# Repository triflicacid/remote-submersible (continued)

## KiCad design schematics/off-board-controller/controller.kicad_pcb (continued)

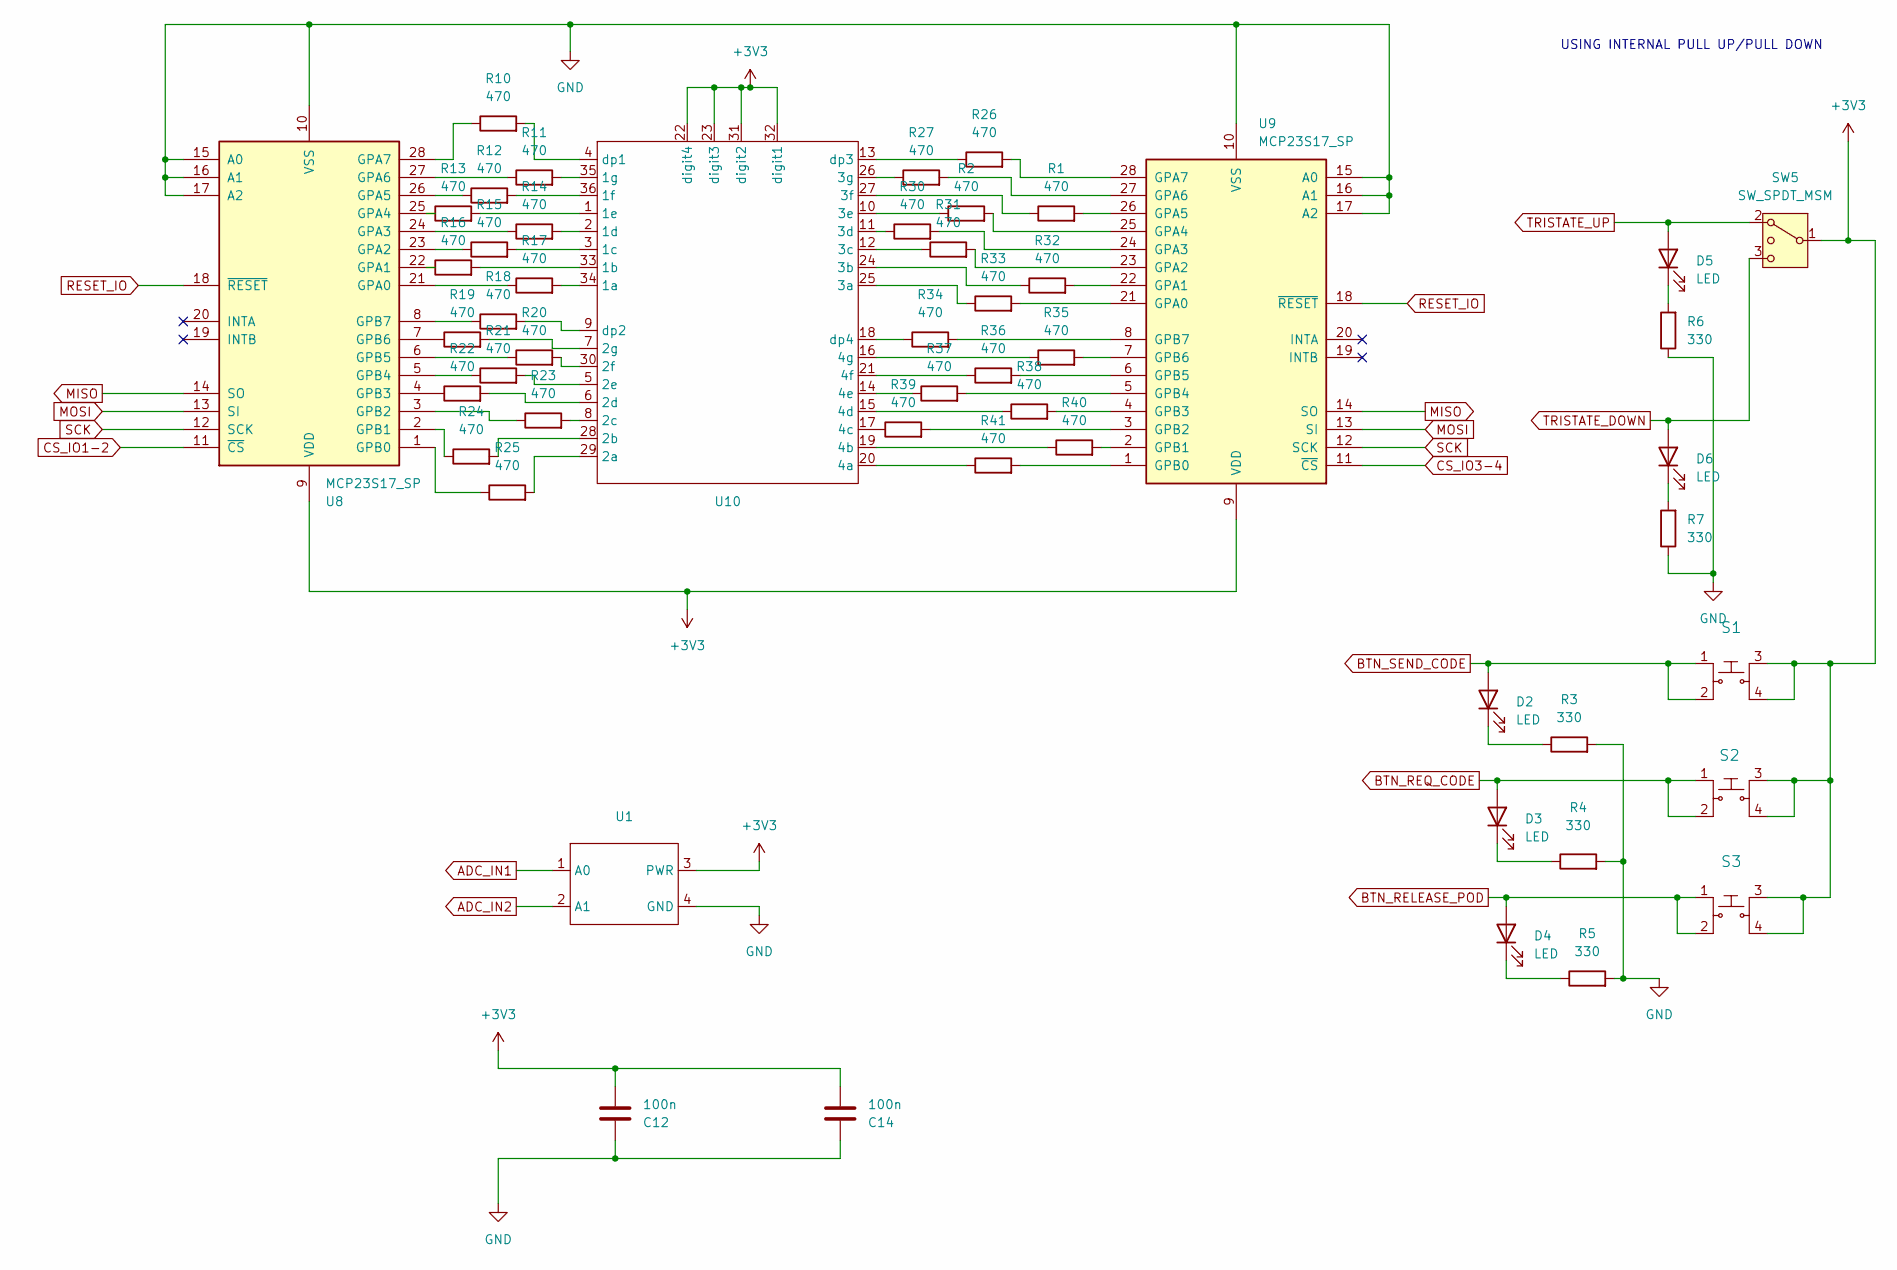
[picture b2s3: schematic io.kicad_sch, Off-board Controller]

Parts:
C12, C14: 100n; C_0805_2012Metric_Pad1.18x1.45mm_HandSolder
D2, D3, D4, D5, D6: LED; LED_0805_2012Metric_Pad1.15x1.40mm_HandSolder
R1, R2, R10, R11, R12, R13, R14, R15, R16, R17, R18, R19, R20, R21, R22, R23, R24, R25, R26, R27, R30, R31, R32, R33, R34, R35, R36, R37, R38, R39, R40, R41: 470; R_0805_2012Metric_Pad1.20x1.40mm_HandSolder
R3, R4, R5, R6, R7: 330; R_0805_2012Metric_Pad1.20x1.40mm_HandSolder
S1, S2, S3: button; MPN 1825910-6; Digi-Key_PN 450-1650-ND
SW5: SW_SPDT_MSM; spdt
U1: NS-Tech_Grove_1x04_P2mm_Vertical
U8, U9: MCP23S17_SP; DIP-28_W7.62mm
U10: seven_segment

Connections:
+3V3: C12.2, C14.2, S1.3, S1.4, S2.3, S2.4, S3.3, S3.4, SW5.1 (3), U1.3 (PWR), U8.9 (VDD), U9.9 (VDD), U10.22 (digit4), U10.23 (digit3), U10.31 (digit2), U10.32 (digit1); also elsewhere on the board
ADC_IN1: U1.1 (A0); also elsewhere on the board
ADC_IN2: U1.2 (A1); also elsewhere on the board
BTN_RELEASE_POD: D4.2 (A), S3.1, S3.2; also elsewhere on the board
BTN_REQ_CODE: D3.2 (A), S2.1, S2.2; also elsewhere on the board
BTN_SEND_CODE: D2.2 (A), S1.1, S1.2; also elsewhere on the board
CS_IO1-2: U8.11 (~CS); also elsewhere on the board
CS_IO3-4: U9.11 (~CS); also elsewhere on the board
GND: C12.1, C14.1, R3.2, R4.2, R5.2, R6.1, R7.1, U1.4 (GND), U8.10 (VSS), U8.15 (A0), U8.16 (A1), U8.17 (A2), U9.10 (VSS), U9.15 (A0), U9.16 (A1), U9.17 (A2); also elsewhere on the board
MISO: U8.14 (SO), U9.14 (SO); also elsewhere on the board
MOSI: U8.13 (SI), U9.13 (SI); also elsewhere on the board
unnamed: D2.1 (K), R3.1
unnamed: D3.1 (K), R4.1
unnamed: D4.1 (K), R5.1
unnamed: D5.1 (K), R6.2
unnamed: D6.1 (K), R7.2
unnamed: R17.1, U8.21 (GPA0)
unnamed: R16.1, U8.22 (GPA1)
unnamed: R15.1, U8.23 (GPA2)
unnamed: R14.1, U8.24 (GPA3)
unnamed: R13.1, U8.25 (GPA4)
unnamed: R12.1, U8.26 (GPA5)
unnamed: R11.1, U8.27 (GPA6)
unnamed: R10.1, U8.28 (GPA7)
unnamed: R25.1, U8.1 (GPB0)
unnamed: R24.1, U8.2 (GPB1)
unnamed: R23.1, U8.3 (GPB2)
unnamed: R22.1, U8.4 (GPB3)
unnamed: R21.1, U8.5 (GPB4)
unnamed: R20.1, U8.6 (GPB5)
unnamed: R19.1, U8.7 (GPB6)
unnamed: R18.1, U8.8 (GPB7)
unnamed: R33.2, U9.21 (GPA0)
unnamed: R32.2, U9.22 (GPA1)
unnamed: R31.2, U9.23 (GPA2)
unnamed: R30.2, U9.24 (GPA3)
unnamed: R2.2, U9.25 (GPA4)
unnamed: R1.2, U9.26 (GPA5)
unnamed: R27.2, U9.27 (GPA6)
unnamed: R26.2, U9.28 (GPA7)
unnamed: R41.2, U9.1 (GPB0)
unnamed: R40.2, U9.2 (GPB1)
unnamed: R39.2, U9.3 (GPB2)
unnamed: R38.2, U9.4 (GPB3)
unnamed: R37.2, U9.5 (GPB4)
unnamed: R36.2, U9.6 (GPB5)
unnamed: R35.2, U9.7 (GPB6)
unnamed: R34.2, U9.8 (GPB7)
unnamed: R17.2, U10.34 (1a)
unnamed: R16.2, U10.33 (1b)
unnamed: R15.2, U10.3 (1c)
unnamed: R14.2, U10.2 (1d)
unnamed: R13.2, U10.1 (1e)
unnamed: R12.2, U10.36 (1f)
unnamed: R11.2, U10.35 (1g)
unnamed: R25.2, U10.29 (2a)
unnamed: R24.2, U10.28 (2b)
unnamed: R23.2, U10.8 (2c)
unnamed: R22.2, U10.6 (2d)
unnamed: R21.2, U10.5 (2e)
unnamed: R20.2, U10.30 (2f)
unnamed: R19.2, U10.7 (2g)
unnamed: R33.1, U10.25 (3a)
unnamed: R32.1, U10.24 (3b)
unnamed: R31.1, U10.12 (3c)
unnamed: R30.1, U10.11 (3d)
unnamed: R2.1, U10.10 (3e)
unnamed: R1.1, U10.27 (3f)
unnamed: R27.1, U10.26 (3g)
unnamed: R41.1, U10.20 (4a)
unnamed: R40.1, U10.19 (4b)
unnamed: R39.1, U10.17 (4c)
unnamed: R38.1, U10.15 (4d)
unnamed: R37.1, U10.14 (4e)
unnamed: R36.1, U10.21 (4f)
unnamed: R35.1, U10.16 (4g)
unnamed: R10.2, U10.4 (dp1)
unnamed: R18.2, U10.9 (dp2)
unnamed: R26.1, U10.13 (dp3)
unnamed: R34.1, U10.18 (dp4)
RESET_IO: U8.18 (~RESET), U9.18 (~RESET); also elsewhere on the board
SCK: U8.12 (SCK), U9.12 (SCK); also elsewhere on the board
TRISTATE_DOWN: D6.2 (A), SW5.3 (4); also elsewhere on the board
TRISTATE_UP: D5.2 (A), SW5.2 (1); also elsewhere on the board

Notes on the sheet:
USING INTERNAL PULL UP/PULL DOWN

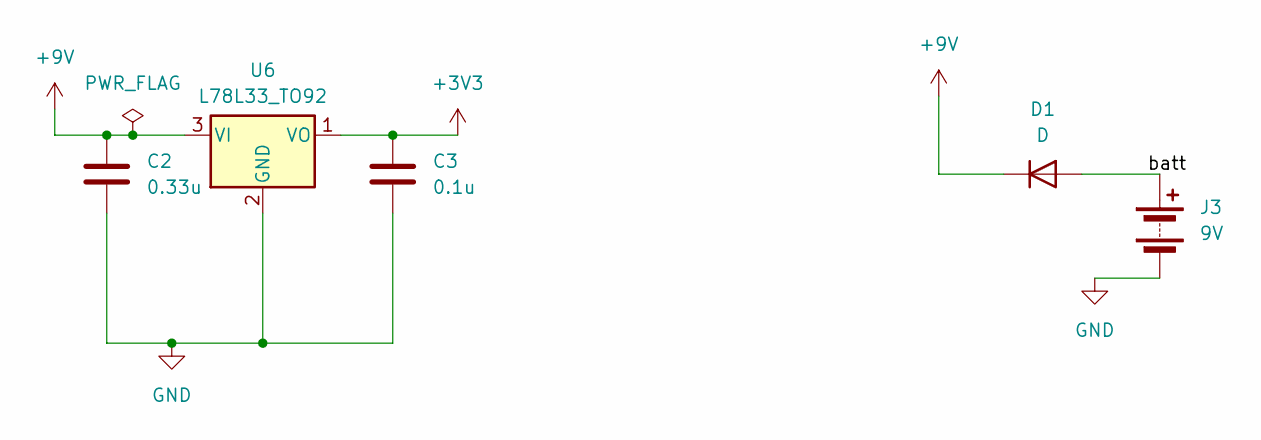
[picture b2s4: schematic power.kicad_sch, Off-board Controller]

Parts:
C2: 0.33u; C_0805_2012Metric_Pad1.18x1.45mm_HandSolder
C3: 0.1u; C_0805_2012Metric_Pad1.18x1.45mm_HandSolder
D1: D; D_A-405_P7.62mm_Horizontal
J3: 9V; PinSocket_1x02_P2.54mm_Vertical
U6: L78L33_TO92; TO-92_Inline

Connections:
+3V3: C3.1, U6.1 (VO); also elsewhere on the board
+9V: C2.1, D1.1 (K), U6.3 (VI)
/power/batt: D1.2 (A), J3.1 (+)
GND: C2.2, C3.2, J3.2 (-), U6.2 (GND); also elsewhere on the board

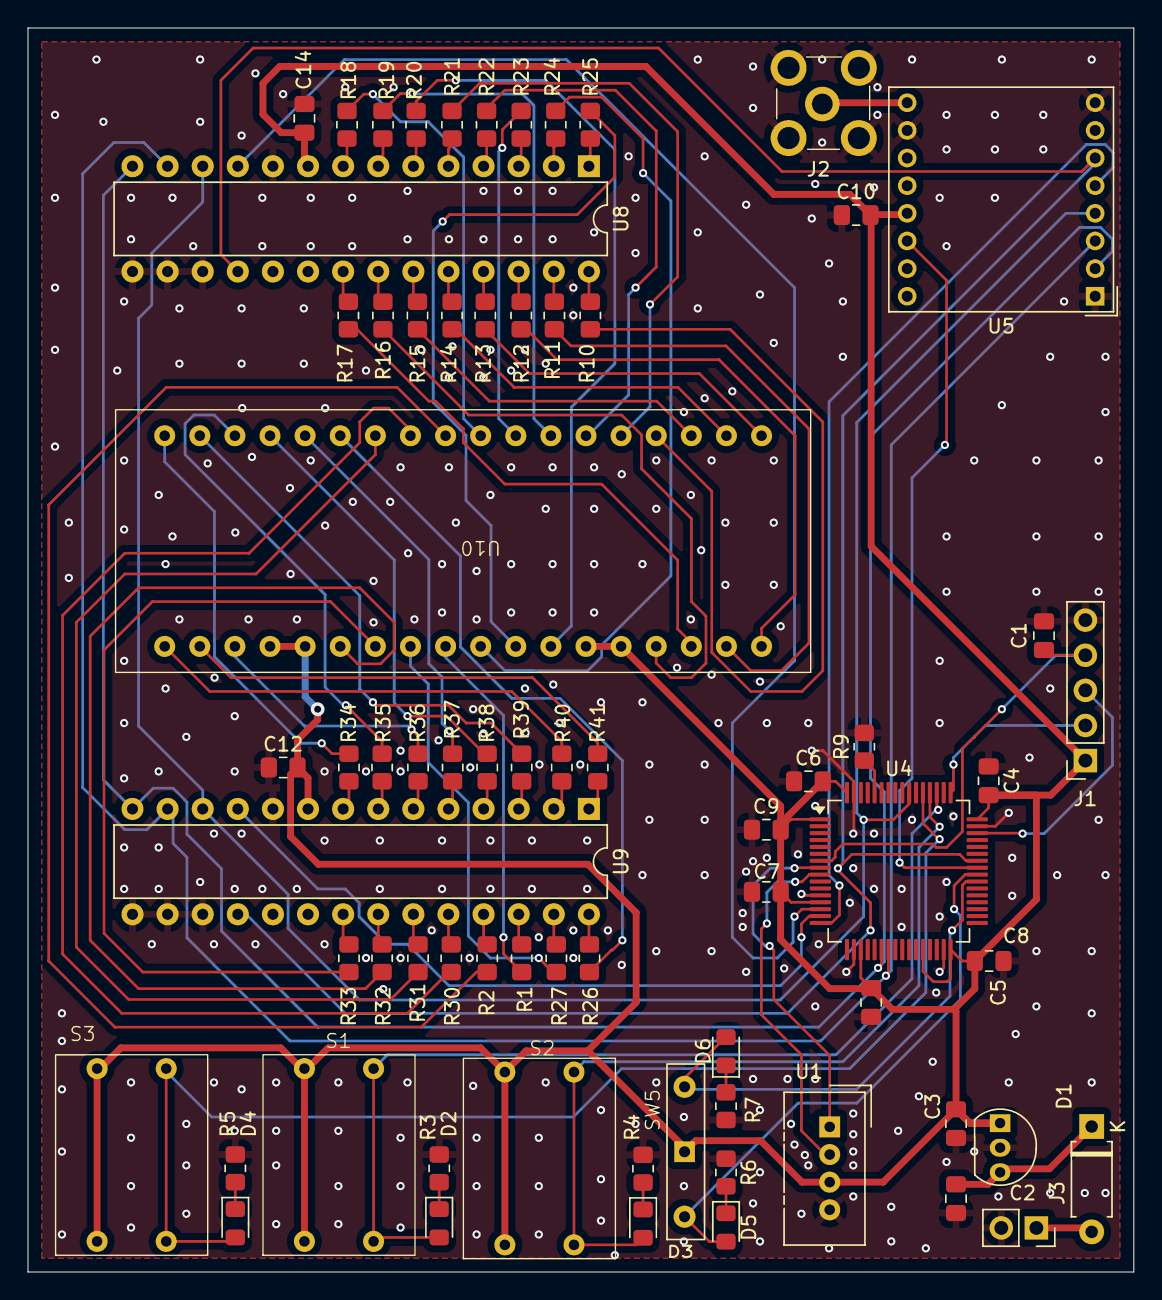
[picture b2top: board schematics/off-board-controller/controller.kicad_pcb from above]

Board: 2 copper layers, 80.0 x 90.0 mm, 70 parts (0 on the bottom side), 93 nets.

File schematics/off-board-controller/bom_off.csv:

Reference,Value,Datasheet,Footprint,Qty,DNP
"C1,C4,C5,C6,C7,C8,C9,C10,C12,C14",100n,~,Capacitor_SMD:C_0805_2012Metric_Pad1.18x1.45mm_HandSolder,10,
C2,0.33u,~,Capacitor_SMD:C_0805_2012Metric_Pad1.18x1.45mm_HandSolder,1,
C3,0.1u,~,Capacitor_SMD:C_0805_2012Metric_Pad1.18x1.45mm_HandSolder,1,
D1,D,~,Diode_THT:D_A-405_P7.62mm_Horizontal,1,
"D2,D3,D4,D5,D6",LED,~,LED_SMD:LED_0805_2012Metric_Pad1.15x1.40mm_HandSolder,5,
J1,programmer,~,Connector_PinSocket_2.54mm:PinSocket_1x05_P2.54mm_Vertical,1,
J2,5-1814832-1,https://www.te.com/commerce/DocumentDelivery/DDEController?A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,digikey-footprints:RF_SMA_Vertical_5-1814832-1,1,
J3,9V,~,Connector_PinSocket_2.54mm:PinSocket_1x02_P2.54mm_Vertical,1,
"R1,R2,R10,R11,R12,R13,R14,R15,R16,R17,R18,R19,R20,R21,R22,R23,R24,R25,R26,R27,R30,R31,R32,R33,R34,R35,R36,R37,R38,R39,R40,R41",470,~,Resistor_SMD:R_0805_2012Metric_Pad1.20x1.40mm_HandSolder,32,
"R3,R4,R5,R6,R7",330,~,Resistor_SMD:R_0805_2012Metric_Pad1.20x1.40mm_HandSolder,5,
R9,10k,~,Resistor_SMD:R_0805_2012Metric_Pad1.20x1.40mm_HandSolder,1,
"S1,S2,S3,U1,U10",~,,-- mixed values --,5,
SW5,SW_SPDT_MSM,~,sub:spdt,1,
U4,STM32L476RGTx,https://www.st.com/resource/en/datasheet/stm32l476rg.pdf,Package_QFP:LQFP-64_10x10mm_P0.5mm,1,
U5,RFM98W-433S2,https://www.hoperf.com/data/upload/portal/20181127/5bfcdb5e1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,RF_Module:HOPERF_RFM9XW_THT,1,
U6,L78L33_TO92,http://www.st.com/content/ccc/resource/technical/document/da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,Package_TO_SOT_THT:TO-92_Inline,1,
"U8,U9",MCP23S17_SP,http://ww1.microchip.com/downloads/en/DeviceDoc/20001952C.pdf,Package_DIP:DIP-28_W7.62mm,2,

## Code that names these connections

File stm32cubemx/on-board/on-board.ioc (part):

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Mcu.Name=STM32L476R(C-E-G)Tx
Mcu.Package=LQFP64
Mcu.UserName=STM32L476RGTx
PA0.GPIOParameters=GPIO_Label
PA0.GPIO_Label=DC_MOTOR_IN1
PA0.Signal=GPIO_Output
PA1.GPIOParameters=GPIO_Label
PA1.GPIO_Label=DC_MOTOR_IN2
PA1.Signal=GPIO_Output
PA13\ (JTMS-SWDIO).Mode=Serial_Wire
PA13\ (JTMS-SWDIO).Signal=SYS_JTMS-SWDIO
PA14\ (JTCK-SWCLK).Mode=Serial_Wire
PA14\ (JTCK-SWCLK).Signal=SYS_JTCK-SWCLK
PA2.GPIOParameters=GPIO_Label
PA2.GPIO_Label=DC_MOTOR_IN3
PA2.Signal=GPIO_Output
PA3.GPIOParameters=GPIO_Label
PA3.GPIO_Label=DC_MOTOR_IN4
PA3.Signal=GPIO_Output
PA5.GPIOParameters=GPIO_Speed,GPIO_PuPd,GPIO_Label,GPIO_ModeDefaultOutputPP
PA5.GPIO_Label=LD2 [green Led]
PA5.GPIO_ModeDefaultOutputPP=GPIO_MODE_OUTPUT_PP
PA5.GPIO_PuPd=GPIO_NOPULL
PA5.GPIO_Speed=GPIO_SPEED_FREQ_LOW
PA5.Signal=GPIO_Output
PA6.GPIOParameters=GPIO_Label
PA6.GPIO_Label=DC_MOTOR_EN1_2
PA6.Signal=S_TIM3_CH1
PA7.GPIOParameters=GPIO_Label
PA7.GPIO_Label=DC_MOTOR_EN3_4
PA7.Signal=S_TIM3_CH2
PB0.GPIOParameters=GPIO_Label
PB0.GPIO_Label=RFM_RESET
PB0.Signal=GPIO_Output
PB1.GPIOParameters=GPIO_Label
PB1.GPIO_Label=RFM_DIO0
PB1.Signal=GPXTI1
PB12.GPIOParameters=GPIO_Label
PB12.GPIO_Label=RFM_SELECT
PB12.Signal=GPIO_Output
PB13.Mode=Full_Duplex_Master
PB13.Signal=SPI2_SCK
PB14.Mode=Full_Duplex_Master
PB14.Signal=SPI2_MISO
PB15.Mode=Full_Duplex_Master
PB15.Signal=SPI2_MOSI
PB3\ (JTDO-TRACESWO).GPIOParameters=GPIO_Label
PB3\ (JTDO-TRACESWO).GPIO_Label=ELECTROMAGNET
PB3\ (JTDO-TRACESWO).Signal=GPIO_Output
PC0.GPIOParameters=GPIO_Label
PC0.GPIO_Label=STEPPER_IN1
PC0.Signal=GPIO_Output
PC1.GPIOParameters=GPIO_Label
PC1.GPIO_Label=STEPPER_IN2
PC1.Signal=GPIO_Output
PC13.GPIOParameters=GPIO_PuPd,GPIO_Label,GPIO_ModeDefaultEXTI
PC13.GPIO_Label=B1 [Blue PushButton]
PC13.GPIO_ModeDefaultEXTI=GPIO_MODE_IT_FALLING
PC13.GPIO_PuPd=GPIO_NOPULL
PC13.Signal=GPXTI13
PC2.GPIOParameters=GPIO_Label
PC2.GPIO_Label=STEPPER_IN3
PC2.Signal=GPIO_Output
PC3.GPIOParameters=GPIO_Label
PC3.GPIO_Label=STEPPER_IN4
PC3.Signal=GPIO_Output
RCC.HSE_VALUE=8000000
RCC.SYSCLKFreq_VALUE=80000000
RCC.SYSCLKSource=RCC_SYSCLKSOURCE_PLLCLK
board=NUCLEO-L476RG
boardIOC=true

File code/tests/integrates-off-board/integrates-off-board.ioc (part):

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Mcu.Name=STM32L476R(C-E-G)Tx
Mcu.Package=LQFP64
Mcu.UserName=STM32L476RGTx
PA0.GPIOParameters=GPIO_Label
PA0.GPIO_Label=CS_IO1_2
PA0.Signal=GPIO_Output
PA1.GPIOParameters=GPIO_Label
PA1.GPIO_Label=CS_IO3_4
PA1.Signal=GPIO_Output
PA13\ (JTMS-SWDIO).Mode=Serial_Wire
PA13\ (JTMS-SWDIO).Signal=SYS_JTMS-SWDIO
PA14\ (JTCK-SWCLK).Mode=Serial_Wire
PA14\ (JTCK-SWCLK).Signal=SYS_JTCK-SWCLK
PA2.GPIOParameters=GPIO_Label
PA2.GPIO_Label=CS_Radio
PA2.Signal=GPIO_Output
PA6.Mode=Full_Duplex_Master
PA6.Signal=SPI1_MISO
PA7.Mode=Full_Duplex_Master
PA7.Signal=SPI1_MOSI
PA8.GPIOParameters=GPIO_Label
PA8.GPIO_Label=Radio_DIO
PA8.Signal=GPIO_Input
PA9.GPIOParameters=GPIO_Label
PA9.GPIO_Label=IO_Reset
PA9.Signal=GPIO_Output
PB3\ (JTDO-TRACESWO).Mode=Full_Duplex_Master
PB3\ (JTDO-TRACESWO).Signal=SPI1_SCK
PC0.Signal=ADCx_IN1
PC1.Signal=ADCx_IN2
PC10.GPIOParameters=GPIO_Label
PC10.GPIO_Label=SendCode
PC10.Signal=GPXTI10
PC11.GPIOParameters=GPIO_Label
PC11.GPIO_Label=RequestCode
PC11.Signal=GPXTI11
PC12.GPIOParameters=GPIO_Label
PC12.GPIO_Label=ReleasePod
PC12.Signal=GPXTI12
PC8.GPIOParameters=GPIO_Label
PC8.GPIO_Label=TriState_Down
PC8.Signal=GPXTI8
PC9.GPIOParameters=GPIO_Label
PC9.GPIO_Label=TriState_Up
PC9.Signal=GPXTI9
RCC.HSE_VALUE=8000000
RCC.SYSCLKFreq_VALUE=80000000
RCC.SYSCLKSource=RCC_SYSCLKSOURCE_PLLCLK
board=custom

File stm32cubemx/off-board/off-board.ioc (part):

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Mcu.Name=STM32L476R(C-E-G)Tx
Mcu.Package=LQFP64
Mcu.UserName=STM32L476RGTx
PA10.GPIOParameters=GPIO_Label
PA10.GPIO_Label=RFM_SELECT
PA10.Signal=GPIO_Output
PA13\ (JTMS-SWDIO).Mode=Serial_Wire
PA13\ (JTMS-SWDIO).Signal=SYS_JTMS-SWDIO
PA14\ (JTCK-SWCLK).Mode=Serial_Wire
PA14\ (JTCK-SWCLK).Signal=SYS_JTCK-SWCLK
PA5.GPIOParameters=GPIO_Speed,GPIO_PuPd,GPIO_Label,GPIO_ModeDefaultOutputPP
PA5.GPIO_Label=LD2 [green Led]
PA5.GPIO_ModeDefaultOutputPP=GPIO_MODE_OUTPUT_PP
PA5.GPIO_PuPd=GPIO_NOPULL
PA5.GPIO_Speed=GPIO_SPEED_FREQ_LOW
PA5.Signal=GPIO_Output
PA6.Mode=Full_Duplex_Master
PA6.Signal=SPI1_MISO
PA7.Mode=Full_Duplex_Master
PA7.Signal=SPI1_MOSI
PA8.GPIOParameters=GPIO_Label
PA8.GPIO_Label=RFM_DIO0
PA8.Signal=GPXTI8
PA9.GPIOParameters=GPIO_Label
PA9.GPIO_Label=RFM_RESET
PA9.Signal=GPIO_Output
PB0.GPIOParameters=GPIO_Label
PB0.GPIO_Label=SSD_SELECT
PB0.Signal=GPIO_Output
PB3\ (JTDO-TRACESWO).Mode=Full_Duplex_Master
PB3\ (JTDO-TRACESWO).Signal=SPI1_SCK
PC0.Signal=SharedAnalog_PC0
PC1.Signal=SharedAnalog_PC1
PC10.GPIOParameters=GPIO_PuPd,GPIO_Label,GPIO_ModeDefaultEXTI
PC10.GPIO_Label=BTN_RELEASE_POD
PC10.GPIO_ModeDefaultEXTI=GPIO_MODE_IT_FALLING
PC10.GPIO_PuPd=GPIO_PULLDOWN
PC10.Signal=GPXTI10
PC11.GPIOParameters=GPIO_PuPd,GPIO_Label,GPIO_ModeDefaultEXTI
PC11.GPIO_Label=BTN_REQ_CODE
PC11.GPIO_ModeDefaultEXTI=GPIO_MODE_IT_FALLING
PC11.GPIO_PuPd=GPIO_PULLDOWN
PC11.Signal=GPXTI11
PC12.GPIOParameters=GPIO_PuPd,GPIO_Label,GPIO_ModeDefaultEXTI
PC12.GPIO_Label=BTN_SEND_CODE
PC12.GPIO_ModeDefaultEXTI=GPIO_MODE_IT_FALLING
PC12.GPIO_PuPd=GPIO_PULLDOWN
PC12.Signal=GPXTI12
PC13.GPIOParameters=GPIO_PuPd,GPIO_Label,GPIO_ModeDefaultEXTI
PC13.GPIO_Label=B1 [Blue PushButton]
PC13.GPIO_ModeDefaultEXTI=GPIO_MODE_IT_FALLING
PC13.GPIO_PuPd=GPIO_NOPULL
PC13.Signal=GPXTI13
PC6.GPIOParameters=GPIO_PuPd,GPIO_Label
PC6.GPIO_Label=TRISTATE_UP
PC6.GPIO_PuPd=GPIO_PULLDOWN
PC6.Signal=GPXTI6
PC7.GPIOParameters=GPIO_PuPd,GPIO_Label
PC7.GPIO_Label=TRISTATE_DOWN
PC7.GPIO_PuPd=GPIO_PULLDOWN
PC7.Signal=GPXTI7
RCC.HSE_VALUE=8000000
RCC.SYSCLKFreq_VALUE=80000000
RCC.SYSCLKSource=RCC_SYSCLKSOURCE_PLLCLK
board=NUCLEO-L476RG
boardIOC=true

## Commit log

2024-07-16 Added README
2024-07-16 Added library timed-events
2024-07-16 Added library action-mgr
2024-07-16 Added stored-code
2024-07-16 Added library 7-segment
2024-07-16 Added library lora
2024-07-16 Added communication
2024-07-16 Added off-board controller schematic
2024-07-16 Controllers: added main
2024-07-16 display_init copies digit_pins buffer
2024-07-16 off-board: set up 7-segment display
2024-07-16 off-board: set up LoRa device
2024-07-16 communication: functions to transmit payload
2024-07-16 off-board: added structure of actions to implement
2024-07-16 off-board: added GPIO_EXTI callback
2024-07-16 off-board: implemented action_ballast
2024-07-16 on-board: initialise LoRa device
2024-07-16 README: added file descriptions
2024-07-16 shared: made _code volatile
2024-07-17 entered initial version of pcb design
2024-07-17 new version, and ltspice for electromagnet
2024-07-17 Added library stepper-motor
2024-07-17 bug fixes and other small changes
2024-07-17 communications: removed malloc from transmit function
2024-07-17 action-mgr: remove malloc, now uses fixed-size array
2024-07-17 timed-events: remove malloc, made fixed-length array. Added support for multiple event arrays.
2024-07-17 Added stepper-event library
2024-07-17 added ifdef macro guards to allow adoption of pre-defined values
2024-07-17 stored-code: extended to allow for storage of multiple codes
2024-07-17 off-board: hardcode internal code, display downloaded code on receive
2024-07-17 controllers: added call to scan timed events in loop
2024-07-18 changed size of electrolytic capacitors
2024-07-18 off-board: added joystick control
2024-07-18 updated names of components on schematic
2024-07-18 started making a new version of off board controller
2024-07-18 updated on-board schematic with changes
2024-07-18 some layout updates
2024-07-19 off-board: added LoRa communication
2024-07-19 fixed .gitignore
2024-07-19 off-board: remove unused second timer
2024-07-19 off-board: remove redundant check in joystick_event_callback
2024-07-19 Added tri-state-switch
2024-07-19 off-board: added depth prediction
2024-07-19 created new version of layout
2024-07-19 updated silkscreen
2024-07-19 updated README to give more structure information
2024-07-19 off-board: added STM32CubeMX configuration
2024-07-19 off-board: modified constants to reflect chip configuration
2024-07-19 off-board: fixed ADC-DMA logic
2024-07-19 7-segment: guarded unnecessary malloc in display_init
2024-07-19 lora: added function to maximise a device's output power
2024-07-19 bug with stack allocation of opaque types (made types visible)
2024-07-19 Added dc-motor library
2024-07-19 on-board: added STM32CubeMX configuration
2024-07-19 on-board: updated schematic to match STM32 confighuration
2024-07-20 off-board: changed location of radio DIO0 and RST pins
2024-07-20 off-board: created schematic
2024-07-20 off-board: added SWCLK and SWDIO needed for the programmer, resolved conflicts
2024-07-20 on-board: added constants, set up timers, set up LoRa
2024-07-20 off-board: removed timed event usage, created seperate timer for depth prediction
2024-07-20 on-board: send & request code handlers
2024-07-20 on-board: release escape pod logic
2024-07-20 on-board: logic to operate propeller DC motors
2024-07-20 dc-motor: cache velocity, guard against repetitious actions
2024-07-20 on-board: logic to operate ballast stepper motor, library fixes
2024-07-20 fixes indentation
2024-07-20 moved global variables to separate globals.h, removed main.h
2024-07-20 code refactor
2024-07-22 started new version
2024-07-22 changed 7-segment library to reflect cyclical updates
2024-07-22 produced version with 2 0V floods
2024-07-22 on-board: pin changes
2024-07-22 added a keepout zone
2024-07-23 changed 7 segment library to 36-pin
2024-07-23 finished footprints, schematic, and started layout
2024-07-23 layout
2024-07-24 made plan for layout
2024-07-24 added some leds to controller
2024-07-27 produced first draft of layout design
2024-07-27 redesigned layout
2024-07-28 first draft of off- board layout
2024-07-29 changed size of holes on buck footprint
2024-07-29 7-segment: added clear function
2024-07-29 LoRa changes
2024-07-29 off-board: changed depth estimation timer to 4Hz
2024-07-29 changed footprint for electrolytic capacitors
2024-07-29 added a bom and edited layout
2024-07-30 added data-store library
2024-07-31 submitted version for checking
2024-08-01 updated footprints for through hole components with long legs
2024-08-01 generated gerber
2024-08-01 off-board: change tri-state switch behaviour to match toggle functionality
2024-08-01 added counter library, excluded .zip files
2024-08-06 Added dock schematic
2024-08-06 off-board: segment movement indicator
2024-08-06 Added TM1637 library
2024-08-07 dock: added code
2024-08-08 added debouncing code for buttons/switch
2024-08-12 off-board: change ADC from circular to normal mode
2024-08-12 added mcp23s17 library for interfacing with the pin extender
2024-08-13 off-board: added 7-segment library
2024-08-14 bug fixes to the TM1637 library
2024-08-15 off-board: generated chip source code
2024-08-15 on-board: generated chip source code
2024-08-15 dock: generated chip source code
2024-08-29 files from vanilla laptop
2024-08-29 Updates to LoRa library
2024-08-30 changes to simulation for electromagnet circuit
2024-08-30 Updated code for LoRa tests
2024-09-02 Added LoRa module tests
2024-09-04 Added various tests, started work on off-board controller
2024-09-05 pinout for on-board
2024-09-05 stepper test had errors, corrected by setting microsteps to 8
2024-09-05 Added integrated code (start of it)
2024-09-06 some changes to electromagnet test
2024-09-06 new lora off-board file
2024-09-06 Added test for LoRa off-board with new library
2024-09-06 fixed radio on integrated
2024-09-06 various changes
2024-09-07 Added dock code
2024-09-07 reset timer for each release electromagnet (stop timer does not reset), though does not work properly on startup
2024-09-07 fixed startup issues for timer, is now very reliable
2024-09-07 code is more reliable when adding appropriate delays in spi communication (on-board)
2024-09-07 copied delays into off-board
2024-09-07 code to stop immediate triggering of timer
2024-09-07 code to stop immediate interrupt for stepper (as in electromagnet)
2024-09-07 disable interrupts for mcp spi
2024-09-07 improved reliability with delay in main loop
2024-09-08 enabled a transmit when requesting a code (was disabled for debugging purposes)
2024-09-08 attempted to fix dma. but still doesn't work (only does one conversion)
2024-09-08 changed setting adc dma, adcs now continuously convert
2024-09-08 depower all stepper pins after movement
2024-09-08 no major changes
2024-09-08 solution for entering hard fault on motor control, but do not understand why it works, solution is untidy
2024-09-08 slightly better solution, but still don't know why it works
2024-09-08 updated range adcs are mapped to to -1 to 1, also updated some max and min adc values
2024-09-08 pwm uses timer 2 not 3
2024-09-09 Small changes to on- and off-board controller
2024-09-09 increases off-board timer to every 0.4s, makes code not get stuck in adding actions
2024-09-09 inverted electromagnet
2024-09-09 increased prescalar of off-board timer
2024-09-09 no changes
2024-09-10 Optimised data transmission, set spreading factor to 12
2024-09-10 Fixed ADC check issue overstraining the chip
2024-09-10 turn off when changing direction
2024-09-10 reduced ballast movement
2024-09-11 final version used in demonstration
2024-09-29 tidied folder structure
